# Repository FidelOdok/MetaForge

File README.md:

# MetaForge

**Describe the hardware you want. MetaForge designs it with you, step by step, and shows its work.**

MetaForge is a control plane for hardware design that runs on your own machine.
You give it a goal and the limits that matter (size, mass, load, budget, standards).
It works through a design flow with specialist AI agents, using real engineering
tools (KiCad, FreeCAD, CadQuery, CalculiX, SPICE, OpenFOAM, Blender). Every result
is saved, versioned and open to review, and nothing is accepted until a person approves it.

> **The prime rule:** if it can't be versioned, reviewed and built, MetaForge doesn't output it.

*An enclosure built through the CAD adapter. Every part is named, carries the material
it was assigned and the dimensions it came out at, and links to the STEP file it was read from.*

**Contents:**
[What is it](#1-what-is-metaforge) ·
[Who is it for](#2-who-is-it-for) ·
[What you can do](#3-what-can-you-do-with-it) ·
[Example](#4-a-simple-example-from-request-to-result) ·
[Quick start](#5-quick-start) ·
[Using it](#6-using-metaforge) ·
[Understanding results](#7-understanding-the-results) ·
[Features today](#8-features-available-today) ·
[Limitations](#9-limitations-and-human-review) ·
[Examples](#10-examples-and-tutorials) ·
[FAQ](#11-frequently-asked-questions) ·
[Troubleshooting](#12-troubleshooting-and-support) ·
[Privacy](#13-data-and-privacy) ·
[Developer setup](#14-developer-setup) ·
[Technical overview](#15-technical-overview-and-integrations) ·
[Roadmap](#16-roadmap) ·
[Contributing](#17-contributing) ·
[Licence](#18-licence-and-third-party-notices)

---

## 1. What is MetaForge?

Designing a physical product means keeping many things consistent at once: the
mechanical parts, the circuit board, the firmware, the analysis that says it will not
break, and the paperwork. Normally these live in separate tools and separate heads.

MetaForge puts them in one place:

- **You say what you want**, in plain language, with the constraints that matter.
- **AI agents do the legwork**: they draw CAD, check circuits, run stress and
  airflow analysis, source parts and write test plans, by driving the same tools an
  engineer would.
- **Everything is recorded** in a *digital twin*: a versioned graph that links each
  requirement to the part that meets it and the evidence that proves it.
- **You stay in charge.** The work stops at review gates. You approve, ask for a
  retry, send it back for rework, or reject.

MetaForge does not replace engineering judgement or physical testing. It does the
repetitive work and keeps the record, so your attention goes to the decisions.

## 2. Who is it for?

| If you are... | MetaForge gives you... |
|---|---|
| **A hardware engineer or small team** (drones, IoT, embedded products, enclosures, brackets) | A first draft of CAD, electronics, BOM and analysis to review and correct, with the evidence attached |
| **A maker or founder without a full engineering team** | A guided route from idea to a buildable design, with checks and warnings where you would otherwise guess |
| **An engineering lead who must sign off** | An audit trail: who approved what, on what evidence, against which requirement |
| **A developer building on AI agents** | An MCP server and plugins that let Claude Code, Codex or your own agent use real engineering tools safely |

You do not need to write code to use the dashboard. You do need Docker to run it.

## 3. What can you do with it?

| Capability | In practice |
|---|---|
| **Turn a goal into a design plan** | Start a design run and get a requirements phase, a design phase and verification, each ending in a review gate |
| **Model parts and assemblies** | Parametric CAD with CadQuery and FreeCAD; every part named, with a library material and its measured dimensions |
| **Check designs with analysis** | Stress and vibration (CalculiX), circuits (SPICE), steady internal airflow (OpenFOAM), mesh convergence checks |
| **Design electronics** | Schematic and board checks (KiCad ERC/DRC), BOM and Gerber export, and generated starter projects |
| **Source parts** | Live stock and price lookups from Digi-Key, Mouser, Nexar, Farnell and Arrow when you add the keys |
| **Choose how to make it** | Rank manufacturing processes for your quantity and material, then review the design against the chosen process |
| **Render it** | Rendered images with Blender, in the materials you assigned |
| **Keep a trail** | Requirements, decisions, evidence, baselines and every agent session are stored and searchable |
| **Use your own AI agent** | Claude Code and Codex plugins expose the same tools; writes are held for your approval |

## 4. A simple example: from request to result

**The request.** You want a protective enclosure for a Raspberry Pi 5.

**1. Ask.** In the dashboard choose *New design run*, pick a project and describe the
intent. Or from a terminal:

```bash
forge design --flow mech_v1 "a printable PLA enclosure for a Raspberry Pi 5, \
  with ventilation, mounting for the board's four screw holes, and a 2 mm wall"
```

`mech_v1` is the flow for a load-bearing part or mechanical subsystem. Its phases are
*Requirements*, *Manufacturing Route and Process Selection*, *Mechanical Design*,
*DFM Review and Manufacturing Plan* and *Simulation and V&V*.

**2. Watch it work.** The run page shows each phase, the tools being called and the
parts appearing in the twin as they are committed.

**3. Review at each gate.** When a phase finishes the run waits for you. The
*Approvals* page shows what was produced, the checks that passed or failed, and why
the gate is held. You approve, retry, send the phase back for rework, or reject.

**4. Read the result.** Open the digital twin to see the model and its record.

**5. Build or iterate.** Export the STEP, GLB, STL or BOM, print a fit coupon, or go
round the loop again with a change.

Here is the same run as a sequence of events:

## 5. Quick start

**You need:** Docker with Compose, and room for it: the stack is many containers,
and the optional CFD adapter alone reserves 12 GB of memory. MetaForge is developed
and tested on Linux and on Windows through WSL 2. For the AI features, an API key from
a model provider (Anthropic, OpenAI or OpenRouter), or a ChatGPT/Codex subscription.

**One command** installs the stack, the `forge` command and your first project:

```bash
curl -fsSL https://raw.githubusercontent.com/FidelOdok/MetaForge/main/scripts/install.sh | bash
```

It is safe to run again. It asks eight things in order:

| Step | What it does |
|---|---|
| 1. Mode | *usage* (built images, generated secrets) or *develop* (editable source, hot reload) |
| 2. Tool adapters | Which of KiCad, CalculiX, CadQuery and FreeCAD to start (skip any you do not need) |
| 3. Preflight | Checks for Docker Compose and a suitable Python |
| 4. Model provider | An API key, a ChatGPT/Codex sign-in, or configure it later |
| 5. Secrets | Generates every password into `.env` (permissions 600) |
| 6. Start the stack | Pulls the gateway image, starts the services and waits until they are healthy |
| 7. `forge` CLI | Installs the command-line tool |
| 8. First project | Creates a project and runs a demo chat turn |

Only the command-line tool: add `-s -- --cli-only` after `bash`. Every flag, including
unattended installs, is listed by `scripts/install.sh --help`.

**Check it worked:**

```bash
curl -s http://localhost:8000/health          # the gateway answers
forge projects list                           # your first project is there
```

Open the dashboard at **http://localhost:3000**. Then start with a conversation
(`forge chat`) or a design run (`forge design "..."`).

## 6. Using MetaForge

**Everyday actions**

| I want to... | Dashboard | Terminal |
|---|---|---|
| Start a design | *New design run* (`/runs/new`) | `forge design "<goal>"` |
| See what needs my decision | *Approvals* | `forge approvals` |
| Approve or reject a gate | Approve, retry, rework or reject on the card | `forge runs approve <id>` / `forge runs reject <id>` |
| Look at the model | *Twin* | `forge twin ...` |
| Ask a question about the design | The conversation drawer on *Twin* | `forge chat --project <id>` |
| Check the bill of materials | *BOM* | |
| Add reference documents | *Knowledge* | `forge ingest <file>` |
| Review what an agent did | *Sessions* | |
| See requirement and gate status | *Requirements*, *Run detail* | `forge runs get <id>` |

**Where things are.** Twenty routes, grouped by purpose:

Every page is described in the [dashboard tour](docs/dashboard-tour.md).

**The terminal** has an interactive assistant too (`forge chat`) that calls tools and
answers from what they return:

**Reviewing results.** Treat every gate as a code review. Open the card, read the
findings, look at the model, and decide. The dashboard sends your decision to the
gateway, which records who decided, from where, and on what.

## 7. Understanding the results

| You will see | It means |
|---|---|
| **Work product** | Anything MetaForge produced or you imported: a CAD model, a schematic, a BOM, a simulation result, a decision |
| **Revision, `KEY@n`** | A work product is an *item* with numbered revisions. Reviewing means comparing `@2` with `@1` |
| **Draft** | Produced during a run and not yet accepted. Drafts become the baseline only when you approve the gate |
| **Gate** | A pause where a person decides. Approve, retry, rework (send back to an earlier phase) or reject |
| **Evidence** | A real tool result: a stress run, an ERC report, a measurement. Evidence records which design revision it analysed |
| **Stale** | The design changed after the evidence was produced. The claim it supported is no longer proven |
| **pass / fail / uncertain / no data** | The verdict on a requirement. *No data* is not a pass: it means nothing has measured it yet |
| **Constraint** | A limit the design must meet (mass, deflection, safety factor). Checked against evidence |
| **DFM verdict** | *manufacturable*, *not manufacturable* or *incomplete* (with what is unknown) for the chosen process |
| **Held call** | An agent tried to write something and is waiting for your approval. It appears on *Approvals* |
| **Material figure** | A strength or density taken from the material library, never guessed. A missing figure is reported as unknown |

**Warnings to take seriously.** "Objective NOT met" in a gate summary, a requirement
with *no data*, evidence marked *stale*, a mesh that has not converged, and any
number shown with no source.

## 8. Features available today

Status is stated plainly. **Working** means it is built, tested and used end to end.
**Early** means it runs but is narrow or not yet proven. **Experimental** means
expect rough edges.

| Area | Status | Notes |
|---|---|---|
| Dashboard (20 routes), `forge` CLI and interactive TUI | Working | |
| Design flows: `design_v1`, `hardware_v1`, `mech_v1`, gates, retry and rework | Working | Flows are versioned and frozen at approval |
| Digital twin: items, revisions, baselines, requirements, evidence | Working | Neo4j and Postgres |
| CAD authoring (CadQuery, FreeCAD), STEP and GLB viewer, named parts and library materials | Working | Part colours come from the STEP file |
| Structural analysis (CalculiX): static, modal, thermal | Working | Check mesh convergence yourself |
| Circuit simulation (SPICE) | Working | |
| Schematic and board checks (KiCad ERC and DRC), BOM and Gerber export | Working | |
| KiCad write: generate a schematic, board and routed layout from a circuit | Early | Generates *new* project folders only; it never edits your own files |
| Steady internal airflow (OpenFOAM) | Early | On the finest mesh it matched a pipe's pressure drop within 0.1 percent. Turbulence models are **not** validated |
| Manufacturing process ranking and DFM review | Working | Process limits must be sourced; missing ones are reported as unknown |
| Studio renders (Blender) | Working | |
| Part sourcing (Digi-Key, Mouser, Nexar, Farnell, Arrow) | Working | Needs your own API keys |
| Knowledge base (ingest documents and datasheets, search with citations) | Working | |
| Agent session capture and the approvals ledger | Working | |
| Claude Code and Codex plugins (local and over HTTP) | Working | Over HTTP, writes are held for you |
| claude.ai web connector (OAuth) | Early | The custom connector works; the packaged plugin connector is not confirmed |
| Compliance checklists (CE, UKCA, FCC, PSTI) | Early | Coverage tracking. It is **not** certification |
| Gazebo, Isaac Sim, Omniverse USD adapters | Experimental | Opt-in |
| IDE assistants (VS Code, KiCad, FreeCAD plugins) | Experimental | Not updated recently. Do not rely on them |
| Multi-user accounts and hosted service | Not in this repository | See [Open core](#15-technical-overview-and-integrations) |

The full tool-by-tool list, kept current, is the
[capability matrix](docs/capability-matrix.md). At least 113 MCP tools register on a
bare install, and more load as you enable adapters.

## 9. Limitations and human review

**MetaForge produces drafts for an engineer to check. It is not a certifying body and
it does not guarantee a design is safe, legal or buildable.** Before you build,
order parts, fly, or rely on a design:

- **Check the numbers that matter**: loads, materials, wall thicknesses, tolerances,
  clearances, voltage and current limits. Confirm the inputs the agent assumed.
- **Read the evidence, not the summary.** A passing gate means the checks that ran
  passed. Look at which checks ran, and which did not.
- **Verify analysis.** Confirm the mesh converged, the boundary conditions are right
  and the result is plausible against a hand calculation.
- **Treat airflow results with caution.** Only steady, incompressible internal flow
  is supported, and turbulence models are not validated.
- **Check electronics yourself.** ERC and DRC catch rule violations, not bad design.
  Generated KiCad projects are starting points.
- **Confirm part data.** Prices, stock and lead times come from distributors and
  change. Datasheet values come from documents you ingested.
- **Compliance is a checklist, not a certificate.** Regulated products need
  qualified assessment.
- **Test physically.** Print a fit coupon, run a bench test, do a fly or load test.
- **AI can be wrong.** Agents can misread a requirement or invent a value. The
  platform refuses unsourced material figures and holds writes for approval, but a
  person must still decide.

## 10. Examples and tutorials

**Guided projects**

| Start here | What it shows |
|---|---|
| [Getting started](docs/getting-started.md) | Install, ingest a document, search it, in three tracks (CLI, Claude Code, dashboard) |
| [Drone flight controller](examples/drone_flight_controller/README.md) | A full reference project: PRD, constraints, BOM, board and firmware through the whole stack. The demos use mock adapters, so they run without Docker |
| [Project structure](docs/project-structure.md) | How a project's files map into the twin |
| [Dashboard tour](docs/dashboard-tour.md) | Every page, with screenshots |
| [CLI reference](docs/cli-reference.md) | Every command |

**Sample prompts**

```bash
# A mechanical part, with the manufacturing route chosen first
forge design --flow mech_v1 "a 3 mm aluminium bracket that holds a 120 g camera \
  and survives a 4 g shock, machined on a 3-axis mill"

# A complete hardware system: mechanical, electronics, firmware, simulation
forge design --flow hardware_v1 "a 3-inch ducted indoor drone with a flight \
  controller, 250 g all-up mass and a 6 minute flight time"

# A general design with requirements first
forge design --flow design_v1 "a wall-mounted holder for a 10-inch tablet"

# Ask questions of a project
forge chat --project <project-id> --message "Which requirements have no evidence yet?"
```

Ask for one thing at a time and state the limits that matter: mass, loads, size,
material, quantity, how you will make it, and any standard it must meet.

## 11. Frequently asked questions

**Do I need to code?** No, not to use the dashboard or `forge chat`. You need to run
one install command. Developers can script the CLI and the API.

**What files does it understand?** CAD: STEP, GLB, STL and 3MF are viewed in the
dashboard. KiCad projects (`.kicad_sch`, `.kicad_pcb`). Documents: Markdown, PDF
datasheets and CSV can be ingested into the knowledge base. BOMs: CSV.

**What does it cost?** MetaForge is free software under the Apache licence. You pay
your model provider for the AI calls you make (or use a ChatGPT/Codex subscription),
and any distributor or search service you choose to enable. Brave Search has a free
tier. There is no MetaForge subscription for a self-hosted install.

**Does it need a GPU?** No. Blender renders on the CPU, and no adapter requires a GPU.

**Does it work offline?** The stack runs locally. Anything that calls a model
provider, Brave Search or a part distributor needs the internet. Without a model
provider the dashboard and the tools still run, and the assistant does not.

**Which AI models?** Anthropic, OpenAI, OpenRouter, or a ChatGPT/Codex subscription.
You choose and can switch in *Settings*.

**Can my own AI agent use it?** Yes. Install the Claude Code or Codex plugin
([section 15](#15-technical-overview-and-integrations)).

**Is my design sent to a server of yours?** No. See [Data and privacy](#13-data-and-privacy).

**Can it design anything?** No. It focuses on electronics-heavy products and
mechanical parts: drones, IoT devices, embedded boards, enclosures, brackets.
It covers a handful of specialist disciplines, not every engineering field.

**Can it order parts or start a build?** It can look up and compare parts. Any action
with a real-world effect is held for your approval.

## 12. Troubleshooting and support

| Symptom | Try |
|---|---|
| `docker compose` says a password is unset | Run `scripts/install.sh`, or fill the blank credentials in `.env` ([section 14](#14-developer-setup)) |
| The dashboard says *Unavailable* | Check `curl http://localhost:8000/health` and that the containers are healthy with `docker compose ps` |
| A tool you expect is missing | The adapter is probably not enabled or failed to start; see [adapters dropped at startup](docs/troubleshooting.md#adapter-x-dropped-silently-at-startup) |
| An approval does not appear | Check the project filter; items with no project are counted separately |
| A held call times out | Approve it within the window (100 seconds when the client sends no progress) |
| Search returns nothing | Ingest a document first, and check the knowledge service is running |

More in the [troubleshooting guide](docs/troubleshooting.md).

**Getting help.** Search or open an issue on
[GitHub Issues](https://github.com/FidelOdok/MetaForge/issues). Include the output of
`curl -s http://localhost:8000/health`, what you ran, and the log lines around the
failure (`docker compose logs gateway`). Remove any keys first.

## 13. Data and privacy

A self-hosted MetaForge keeps your project data on your own machine or server and
needs no account. A search of the code finds no third-party analytics or
crash-reporting service; telemetry goes to the observability stack you run.

**What is stored, and where**

| Data | Where |
|---|---|
| Projects, runs, sessions, approvals | Postgres |
| The digital twin (items, revisions, requirements, evidence) | Neo4j |
| CAD, renders and result files | The object store (SeaweedFS) |
| Agent sessions and decisions | Postgres, with a record of every tool call |
| Credentials | `.env` on your machine (permissions 600) and the gateway's store |
| Logs, metrics and traces | Loki, Prometheus and Tempo in your stack |

**Who can see it.** With no authentication provider (the default, for a local
single-user setup) anyone who can reach the gateway can read it, so keep it on
localhost or behind your own network controls. For a shared server, set
`METAFORGE_AUTH_MODE`; the gateway then refuses to start unless a provider is
installed ([authentication](docs/deployment/authentication.md)).

**What leaves your machine, and only if you configure it**

| Service | What it receives |
|---|---|
| Your model provider (Anthropic, OpenAI, OpenRouter, Codex) | Your prompts, the project brief, and tool results the assistant reads |
| OpenRouter (optional) | Text sent for knowledge property extraction and component intent search |
| Brave Search (optional) | Web search queries and fetched page requests |
| Part distributors (optional) | Part numbers and quantities |
| GitHub Container Registry | Image pulls during install and update |

Choose a provider whose terms fit your design's confidentiality. Do not put secrets or
export-controlled data into a prompt.

**Export.** Download CAD files (STEP, GLB, STL) and the BOM from the dashboard or the
API (`/v1/cad-export`); Gerbers come from the KiCad export tool. Everything is stored
on your own machine, so you can also copy it directly.

**Delete.** Deleting a project in the dashboard or with `forge projects delete`
removes the **project record only**. Its work products, stored files and run history
are separate. Delete a work product through the twin. To remove everything on a
machine, stop the stack and delete its volumes:

```bash
docker compose down -v        # removes the databases, object store and logs
```

**Retention.** MetaForge sets no automatic expiry on project data, run history,
sessions or logs. Keep, back up or delete them as your policy requires, and take your
own backups. The Claude Code session-capture hook can be turned off with
`METAFORGE_SESSION_CAPTURE=off`.

This repository contains no hosted service, so a self-hosted install has no privacy
policy of ours to accept. The hosted service, where offered, is separate and has its
own terms.

## 14. Developer setup

**Prerequisites:** Git, Docker with Compose, Python 3.11 or later, and Node 22 for the
dashboard and docs site.

**The quick way** (editable install, hot-reload containers, source bind-mounted):

```bash
git clone https://github.com/FidelOdok/MetaForge.git
cd MetaForge
./scripts/install.sh --develop
```

**By hand:**

```bash
git clone https://github.com/FidelOdok/MetaForge.git && cd MetaForge
python -m venv .venv && source .venv/bin/activate
pip install -e ".[dev,knowledge,cadquery]"

cp .env.example .env            # then fill the blank credentials below
docker compose up -d postgres neo4j gateway dashboard
```

Compose refuses to start a service whose password is blank, on purpose, so no install
shares a published default. Generate each one:

```bash
openssl rand -base64 24         # run once per blank value
```

**Configuration.** An example with no secrets (`.env.example` is the full list):

```bash
# Ports
GATEWAY_PORT=8000
DASHBOARD_PORT=3000

# Service credentials: you generate these (leave blank and compose refuses to start)
NEO4J_USER=neo4j
NEO4J_PASSWORD=
POSTGRES_PASSWORD=
MINIO_SECRET_KEY=               # the object store's secret key
TEMPORAL_POSTGRES_PASSWORD=
GRAFANA_PASSWORD=               # only with the observability profile

# Model provider
METAFORGE_LLM_PROVIDER=anthropic    # anthropic | openai | openrouter | openai-codex
METAFORGE_LLM_API_KEY=              # your provider key; none for openai-codex

# Optional services (each adapter turns itself off when its key is absent)
BRAVE_API_KEY=                  # web.search and web.fetch
OPEN_ROUTER_API_KEY=            # knowledge property extraction
DIGIKEY_CLIENT_ID=
DIGIKEY_CLIENT_SECRET=
MOUSER_API_KEY=
NEXAR_CLIENT_ID=
NEXAR_CLIENT_SECRET=
FARNELL_API_KEY=
ARROW_LOGIN=
ARROW_API_KEY=

# Access control
METAFORGE_AUTH_MODE=off         # off for local single-user; a provider name for shared use
METAFORGE_MCP_API_KEY=          # guards the HTTP MCP endpoint; set before exposing it
```

| Credential | What it is for | Where to get it |
|---|---|---|
| `NEO4J_PASSWORD`, `POSTGRES_PASSWORD`, `MINIO_SECRET_KEY`, `TEMPORAL_POSTGRES_PASSWORD`, `GRAFANA_PASSWORD` | Protect the services MetaForge runs for you | You generate them |
| `METAFORGE_LLM_API_KEY` | Calls to your model provider | Anthropic, OpenAI or OpenRouter |
| `BRAVE_API_KEY` | Web search | [brave.com/search/api](https://brave.com/search/api/) |
| Distributor keys | Live stock and price | Each distributor's developer portal |
| `METAFORGE_MCP_API_KEY` | Bearer key for the HTTP MCP endpoint | You generate it |

**Verify:**

```bash
curl -s http://localhost:8000/health | python -m json.tool     # status ok, auth_mode off
python -m cli.forge_cli projects list
cd dashboard && npm install && npm test                        # from the dashboard directory
pytest tests/unit -q
ruff check . && ruff format --check .
```

Dashboard on a hot-reload port: `cd dashboard && npm run dev` serves at
http://localhost:5173. Docs preview: `cd docs-site && npm install && npm start`.

Regenerate a diagram after editing its `.mmd` source in `docs/assets/diagrams/`:
`node scripts/render_diagrams.mjs`.

## 15. Technical overview and integrations

![Architecture: clients (CLI, dashboard, plugins) reach the gateway and the MCP sidecar; the gateway runs design flows on Temporal, which drive domain agents and skills; every tool call goes through the MCP registry to containerised adapters; state lives in the twin, Postgres and an object store; Kafka and the observability stack sit alongside](docs/assets/diagrams/architecture-layers.png)

The rules the design follows: agents never call tools directly (everything passes the
MCP registry); the digital twin owns all state; writes are read-only until a person
approves; and everything is versioned.

**Drive it from your own agent.** MetaForge speaks MCP. Install **one** package:

```
/plugin marketplace add FidelOdok/MetaForge
/plugin install metaforge          # reaches a gateway over HTTP, signs in with OAuth
```

```
pipx install "git+https://github.com/FidelOdok/MetaForge.git"
/plugin marketplace add FidelOdok/MetaForge
/plugin install metaforge-local    # runs on this machine, no gateway
```

Over HTTP a tool that writes is held for a human on the *Approvals* page. The local
package treats a stdio session as the engineer at the machine, so its writes run
unheld unless your client supports inline MCP elicitation. Either way the server
enforces it. A third package, `metaforge-cloud`, is the HTTP one with the hosted
gateway's address built in. claude.ai and ChatGPT run in someone else's datacentre
and cannot reach `localhost`; read the
[hosted harness guide](docs/integrations/hosted-harness.md) first.

**Technical documentation**

- [Architecture](docs/architecture.md) and [the agent harness](docs/architecture/robust-harness-design.md)
- [Supported integrations](docs/integrations/claude-code.md): [Claude Code](docs/integrations/claude-code.md), [Codex](docs/integrations/codex.md), [MCP config examples](docs/integrations/mcp-config-examples.md)
- API and MCP: [gateway API reference](docs/reference/gateway-api.md), [MCP specification](docs/mcp_spec.md), [capability matrix](docs/capability-matrix.md)
- [Authentication and permissions](docs/deployment/authentication.md) and [approvals](docs/approvals.md)
- [Deployment](docs/deployment/image-only-host.md), [verifying images](docs/deployment/verifying-images.md)
- [Digital twin schema](docs/twin_schema.md) and [skill specification](docs/skill_spec.md)
- Hosted docs: <https://fidelodok.github.io/MetaForge/>

**Open core.** Everything that turns intent into reviewable hardware is in this
repository: the gateway, orchestrator, digital twin, agents, adapters, dashboard and
CLI. A local single-user MetaForge needs no account. The hosted service (accounts,
identity, control plane) is a separate repository that plugs in through two
provider-neutral seams: the `metaforge.auth` entry-point group on the gateway and the
`metaforge:auth` module alias in the dashboard.

## 16. Roadmap

The [roadmap](docs/roadmap.md) says what is released, in progress, planned and not
started, and how the original four-phase plan compares with what was built. **No
delivery dates are currently agreed.** Nothing on the roadmap should be read as
released unless it is also in the [capability matrix](docs/capability-matrix.md).

**In progress:** work product identity and baselines, skill fidelity, airflow
validation, generative simulation and headless CAD authoring.
**Planned, no date:** manufacturing and vendor integration, a reference library,
policy-based approvals for external agents, the next versions of the Claude Code and
Codex plugins, robot-grade simulation, and a layout that scales to large twins.
**Not started:** most of the 25 engineering disciplines; seven have agents today.

## 17. Contributing

Outside contributions are welcome. Report a bug or suggest a change on
[GitHub Issues](https://github.com/FidelOdok/MetaForge/issues). For code, read
[`CONTRIBUTING.md`](CONTRIBUTING.md) for setup, standards and the checks a pull
request must pass, then [`CLAUDE.md`](CLAUDE.md) for the architecture, testing and
observability requirements. Everyone taking part follows the
[Code of Conduct](CODE_OF_CONDUCT.md). By contributing you license your work under
the Apache License 2.0.

Day-to-day planning happens in a private tracker, so internal task references in
history will not resolve for you. Nothing needed to review a change depends on them.

## 18. Licence and third-party notices

MetaForge is published at [metaforge.uk](https://www.metaforge.uk) and
is licensed under the [Apache License 2.0](LICENSE). Attribution is in
[`NOTICE`](NOTICE).

Tools that MetaForge drives, and services it depends on, are separate programs with
their own licences, for example KiCad, FreeCAD, CalculiX, OpenFOAM and Blender. They
run in their own containers or processes and exchange files with MetaForge. Check each
project's licence before you redistribute an image that includes one. Reference
datasheets cached under `tests/fixtures/datasheets/` are excerpted for technical
testing only; the original vendor copyrights apply (see
`tests/fixtures/datasheets/README.md`). A complete generated inventory of dependency
licences is not yet published.

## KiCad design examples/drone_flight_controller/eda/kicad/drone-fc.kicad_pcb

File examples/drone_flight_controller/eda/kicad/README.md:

# KiCad project — generated reference board

This is the drone flight controller as MetaForge's Phase 2 electronics pipeline
generates it (FORGE-685). Nothing here was drawn by hand:

| File | What it is |
|------|------------|
| `drone-fc.kicad_sch` | Schematic from `kicad.generate_schematic` |
| `drone-fc.kicad_pcb` | 4-layer board from `kicad.generate_pcb`, routed by `kicad.autoroute_pcb` |
| `drone-fc.kicad_pro`, `sym-lib-table`, `fp-lib-table` | Project and library tables |
| `drone-fc-top.png` | Top render (`kicad.render_pcb`) |
| `report.json` | Every check result from the run that produced these files |

The input is [`../circuit.json`](../circuit.json), written by
[`../build_circuit.py`](../build_circuit.py) from the design by pin *name*
(`U1:PA5`), with each name resolved to the pin number in KiCad's own symbol.
To regenerate, run this in the kicad-adapter image:

```bash
python examples/drone_flight_controller/eda/build_circuit.py
python examples/drone_flight_controller/eda/generate.py
```

## The board

- STM32F405RGT6 (LQFP-64) with an 8 MHz crystal, a SWD header and USB FS
  behind a USBLC6 ESD array on a USB-C receptacle.
- MPU-6000 IMU on SPI1, BMP280 barometer on I2C1, and an AP2112K-3.3 LDO
  from the 5 V input (the ESC's BEC, or USB).
- Motor outputs M1–M4 on PB0/PB1 (TIM3) and PA0/PA1 (TIM5), the pins
  [`firmware/src/pinmap.json`](../../firmware/src/pinmap.json) assigns.
- 40 × 40 mm, 4 layers: In1.Cu a solid GND plane and In2.Cu a +3V3 plane
  (decision DD-002), with GND poured on both outer layers. Tracks are 0.15 mm,
  vias 0.5/0.25 mm, and the 5 V input runs at 0.4 mm.

## What the checks say

KiCad runs every check: ERC on the schematic with 0 errors, the exported
netlist matching the circuit net for net, and the routed board at 0
unconnected items and 0 DRC errors, with schematic parity clean. The STEP
export has a model for all 34 parts. `report.json` records the exact counts.

The placement is the generator's deterministic starting point. It puts the
MCU at the centre, the connectors on the left edge, and each part beside the
one it shares the most with, so the decoupling capacitors line up along the
MCU's supply pins. It is a correct board, not a tuned one. Nothing here
claims signal integrity, controlled impedance for the USB pair, or EMC
performance. Those need a field solver and a person.

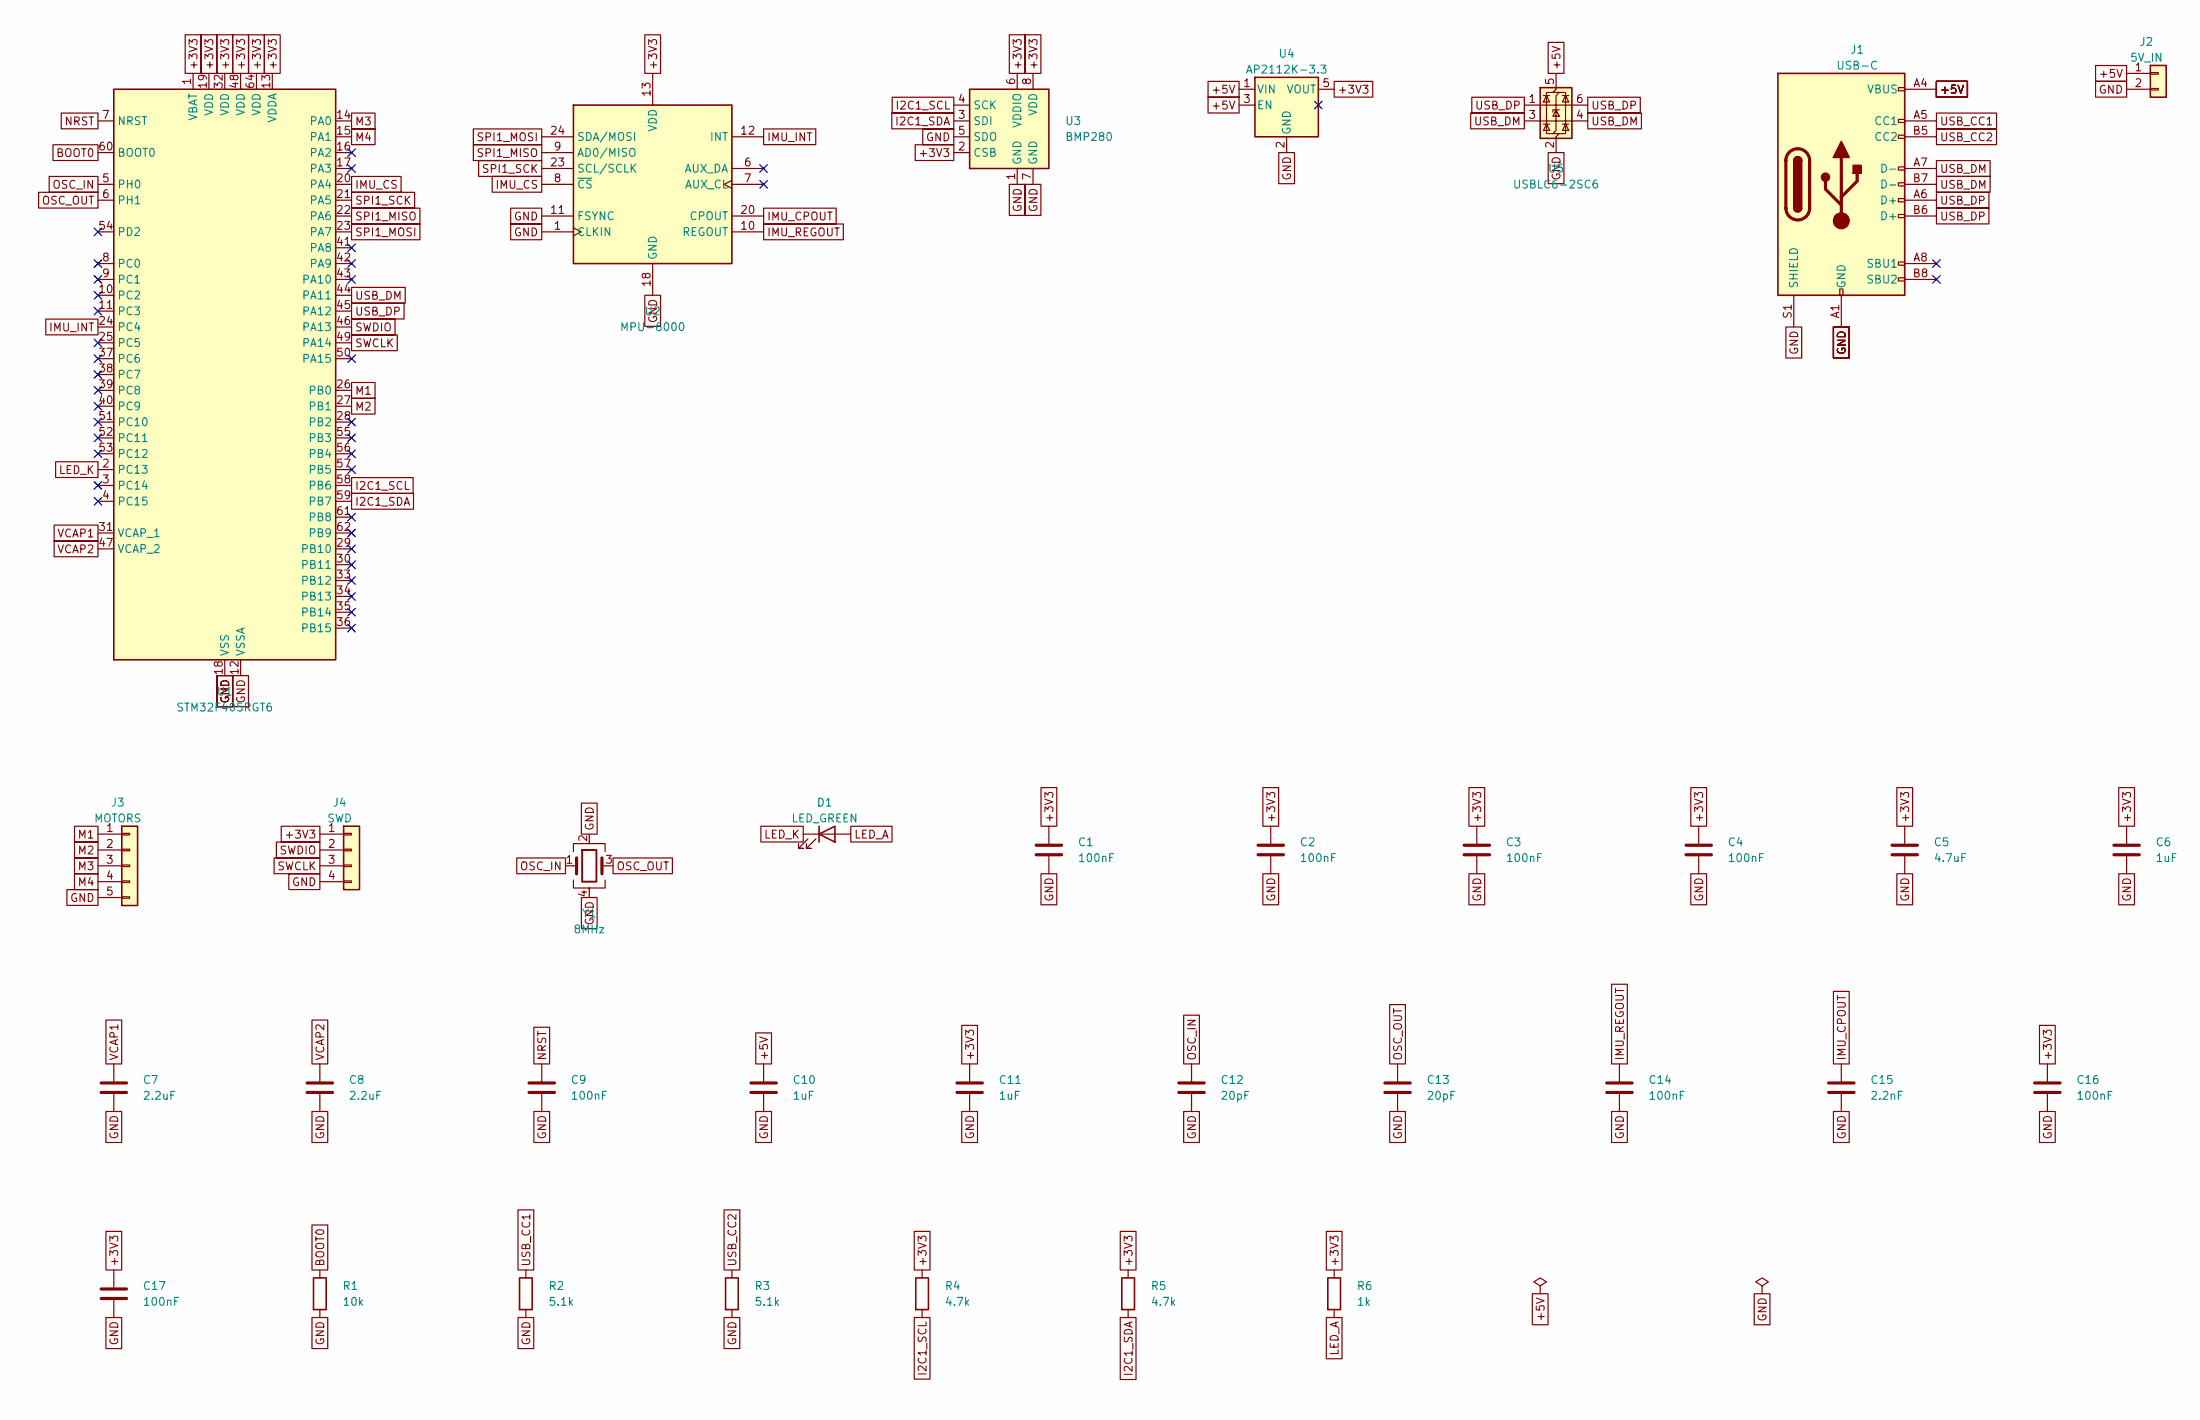
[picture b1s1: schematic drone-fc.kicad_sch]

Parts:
C1, C2, C3, C4, C9, C14, C16, C17: 100nF; C_0402_1005Metric
C5: 4.7uF; C_0603_1608Metric
C6, C10, C11: 1uF; C_0402_1005Metric
C7, C8: 2.2uF; C_0402_1005Metric
C12, C13: 20pF; C_0402_1005Metric
C15: 2.2nF; C_0402_1005Metric
D1: LED_GREEN; LED_0603_1608Metric
J1: USB-C; USB_C_Receptacle_GCT_USB4105-xx-A_16P_TopMnt_Horizontal; MPN USB4105-GF-A
J2: 5V_IN; JST_PH_B2B-PH-K_1x02_P2.00mm_Vertical
J3: MOTORS; JST_PH_B5B-PH-K_1x05_P2.00mm_Vertical
J4: SWD; PinHeader_1x04_P1.27mm_Vertical
R1: 10k; R_0402_1005Metric
R2, R3: 5.1k; R_0402_1005Metric
R4, R5: 4.7k; R_0402_1005Metric
R6: 1k; R_0402_1005Metric
U1: STM32F405RGT6; LQFP-64_10x10mm_P0.5mm; MPN STM32F405RGT6
U2: MPU-6000; InvenSense_QFN-24_4x4mm_P0.5mm; MPN MPU-6000
U3: BMP280; Bosch_LGA-8_2x2.5mm_P0.65mm_ClockwisePinNumbering; MPN BMP280
U4: AP2112K-3.3; SOT-23-5; MPN AP2112K-3.3TRG1
U5: USBLC6-2SC6; SOT-23-6; MPN USBLC6-2SC6
Y1: 8MHz; Crystal_SMD_3225-4Pin_3.2x2.5mm

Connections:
+3V3: C1.1, C2.1, C3.1, C4.1, C5.1, C6.1, C11.1, C16.1, C17.1, J4.1, R4.1, R5.1, R6.1, U1.1 (VBAT), U1.13 (VDDA), U1.19 (VDD), U1.32 (VDD), U1.48 (VDD), U1.64 (VDD), U2.13 (VDD), U3.2 (CSB), U3.6 (VDDIO), U3.8 (VDD), U4.5 (VOUT)
+5V: C10.1, J1.A4 (VBUS), J1.A9 (VBUS), J1.B4 (VBUS), J1.B9 (VBUS), J2.1, U4.1 (VIN), U4.3 (EN), U5.5 (VBUS)
BOOT0: R1.1, U1.60 (BOOT0)
GND: C1.2, C2.2, C3.2, C4.2, C5.2, C6.2, C7.2, C8.2, C9.2, C10.2, C11.2, C12.2, C13.2, C14.2, C15.2, C16.2, C17.2, J1.A1 (GND), J1.A12 (GND), J1.B1 (GND), J1.B12 (GND), J1.S1 (SHIELD), J2.2, J3.5, J4.4, R1.2, R2.2, R3.2, U1.12 (VSSA), U1.18 (VSS), U1.63 (VSS), U2.1 (CLKIN), U2.11 (FSYNC), U2.18 (GND), U3.1 (GND), U3.5 (SDO), U3.7 (GND), U4.2 (GND), U5.2 (GND), Y1.2, Y1.4
I2C1_SCL: R4.2, U1.58 (PB6), U3.4 (SCK)
I2C1_SDA: R5.2, U1.59 (PB7), U3.3 (SDI)
IMU_CPOUT: C15.1, U2.20 (CPOUT)
IMU_CS: U1.20 (PA4), U2.8 (~CS)
IMU_INT: U1.24 (PC4), U2.12 (INT)
IMU_REGOUT: C14.1, U2.10 (REGOUT)
LED_A: D1.2 (A), R6.2
LED_K: D1.1 (K), U1.2 (PC13)
M1: J3.1, U1.26 (PB0)
M2: J3.2, U1.27 (PB1)
M3: J3.3, U1.14 (PA0)
M4: J3.4, U1.15 (PA1)
NRST: C9.1, U1.7 (NRST)
OSC_IN: C12.1, U1.5 (PH0), Y1.1
OSC_OUT: C13.1, U1.6 (PH1), Y1.3
SPI1_MISO: U1.22 (PA6), U2.9 (AD0/MISO)
SPI1_MOSI: U1.23 (PA7), U2.24 (SDA/MOSI)
SPI1_SCK: U1.21 (PA5), U2.23 (SCL/SCLK)
SWCLK: J4.3, U1.49 (PA14)
SWDIO: J4.2, U1.46 (PA13)
USB_CC1: J1.A5 (CC1), R2.1
USB_CC2: J1.B5 (CC2), R3.1
USB_DM: J1.A7 (D-), J1.B7 (D-), U1.44 (PA11), U5.3 (I/O2), U5.4 (I/O2)
USB_DP: J1.A6 (D+), J1.B6 (D+), U1.45 (PA12), U5.1 (I/O1), U5.6 (I/O1)
VCAP1: C7.1, U1.31 (VCAP_1)
VCAP2: C8.1, U1.47 (VCAP_2)

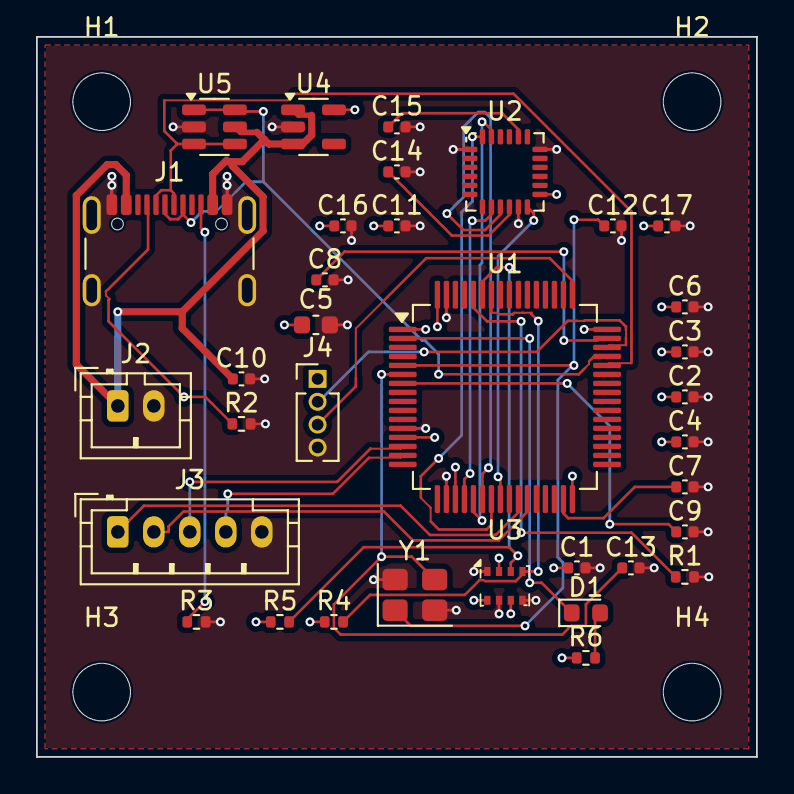
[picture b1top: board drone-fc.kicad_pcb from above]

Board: 4 copper layers, 40.0 x 40.0 mm, 38 parts (0 on the bottom side), 30 nets.

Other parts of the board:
H1, H2, H3, H4: MountingHole_3.2mm_M3

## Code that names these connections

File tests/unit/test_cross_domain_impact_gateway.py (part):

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        pinmap, firmware = _example_files()
        entries = parse_pinmap(pinmap)
        names = pinmap_names(entries)
        assert {"SPI1", "PA5", "I2C1", "PB6", "USART1"} <= names
        refs = firmware_references(names, firmware)
        assert "SPI1" in refs and "src/config.h" in refs["SPI1"]
        assert "I2C1" in refs
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            target_ref=fw_key,
            declared_by="human",
            actor="alice",
            coupled_parameters=["SPI1", "PA5", "PA6", "PA7"],
        )
        build = await _evidence(twin, [fw_key], "firmware.build", {"success": True})
        moved = pinmap["pinmap.json"].replace(b'"pin": "PA2"', b'"pin": "PA0"')
        assert moved != pinmap["pinmap.json"]
        await _revise(
            twin, "pinmap", "FC pin map", files={"pinmap.json": moved}, blobs=blobs, key=pin_key
        )
        assert (await twin.graph.get_node(build)).metadata["staleness"] == "current"
        # Now move an SPI1 pin: the firmware uses it, so its build goes stale.
        spi = moved.replace(b'"pin": "PA5"', b'"pin": "PB3"')
        await _revise(
            twin, "pinmap", "FC pin map", files={"pinmap.json": spi}, blobs=blobs, key=pin_key
        )
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        assert meta["staleness"] == "stale" and meta["stale_for"][pin_key]["current"] == 3
        impacts = await list_impacts(twin, PID)
        assert [i.change.new_ref for i in impacts] == [f"{pin_key}@3"]
        assert impacts[0].change.changed_parameters == ["PA5", "PB3", "SPI1"]

    def test_the_pinmap_diff_names_the_rows_that_changed(self) -> None:
        pinmap, _ = _example_files()
        old = parse_pinmap(pinmap)
        new = parse_pinmap({"pinmap.json": pinmap["pinmap.json"].replace(b'"PA5"', b'"PB3"')})
        assert diff_pinmaps(old, new) == ["PA5", "PB3", "SPI1"]


# ---------------------------------------------------------------------------
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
